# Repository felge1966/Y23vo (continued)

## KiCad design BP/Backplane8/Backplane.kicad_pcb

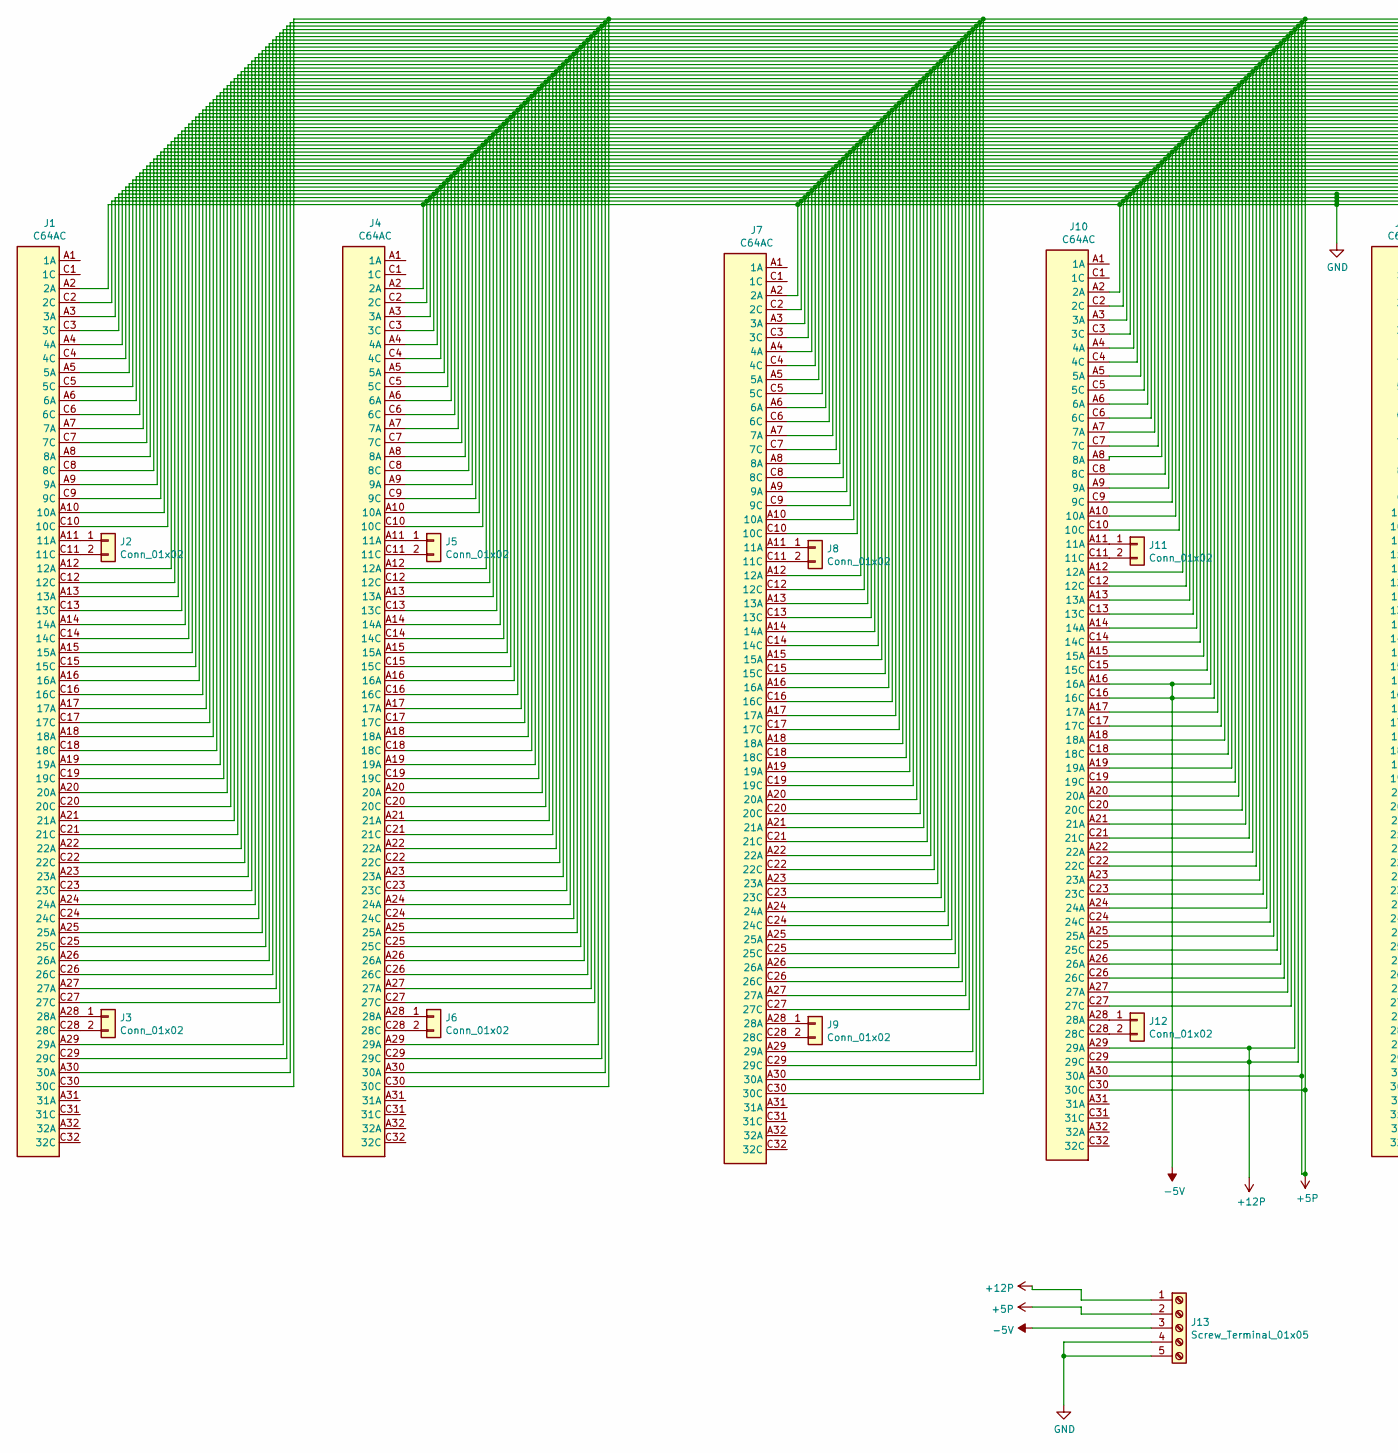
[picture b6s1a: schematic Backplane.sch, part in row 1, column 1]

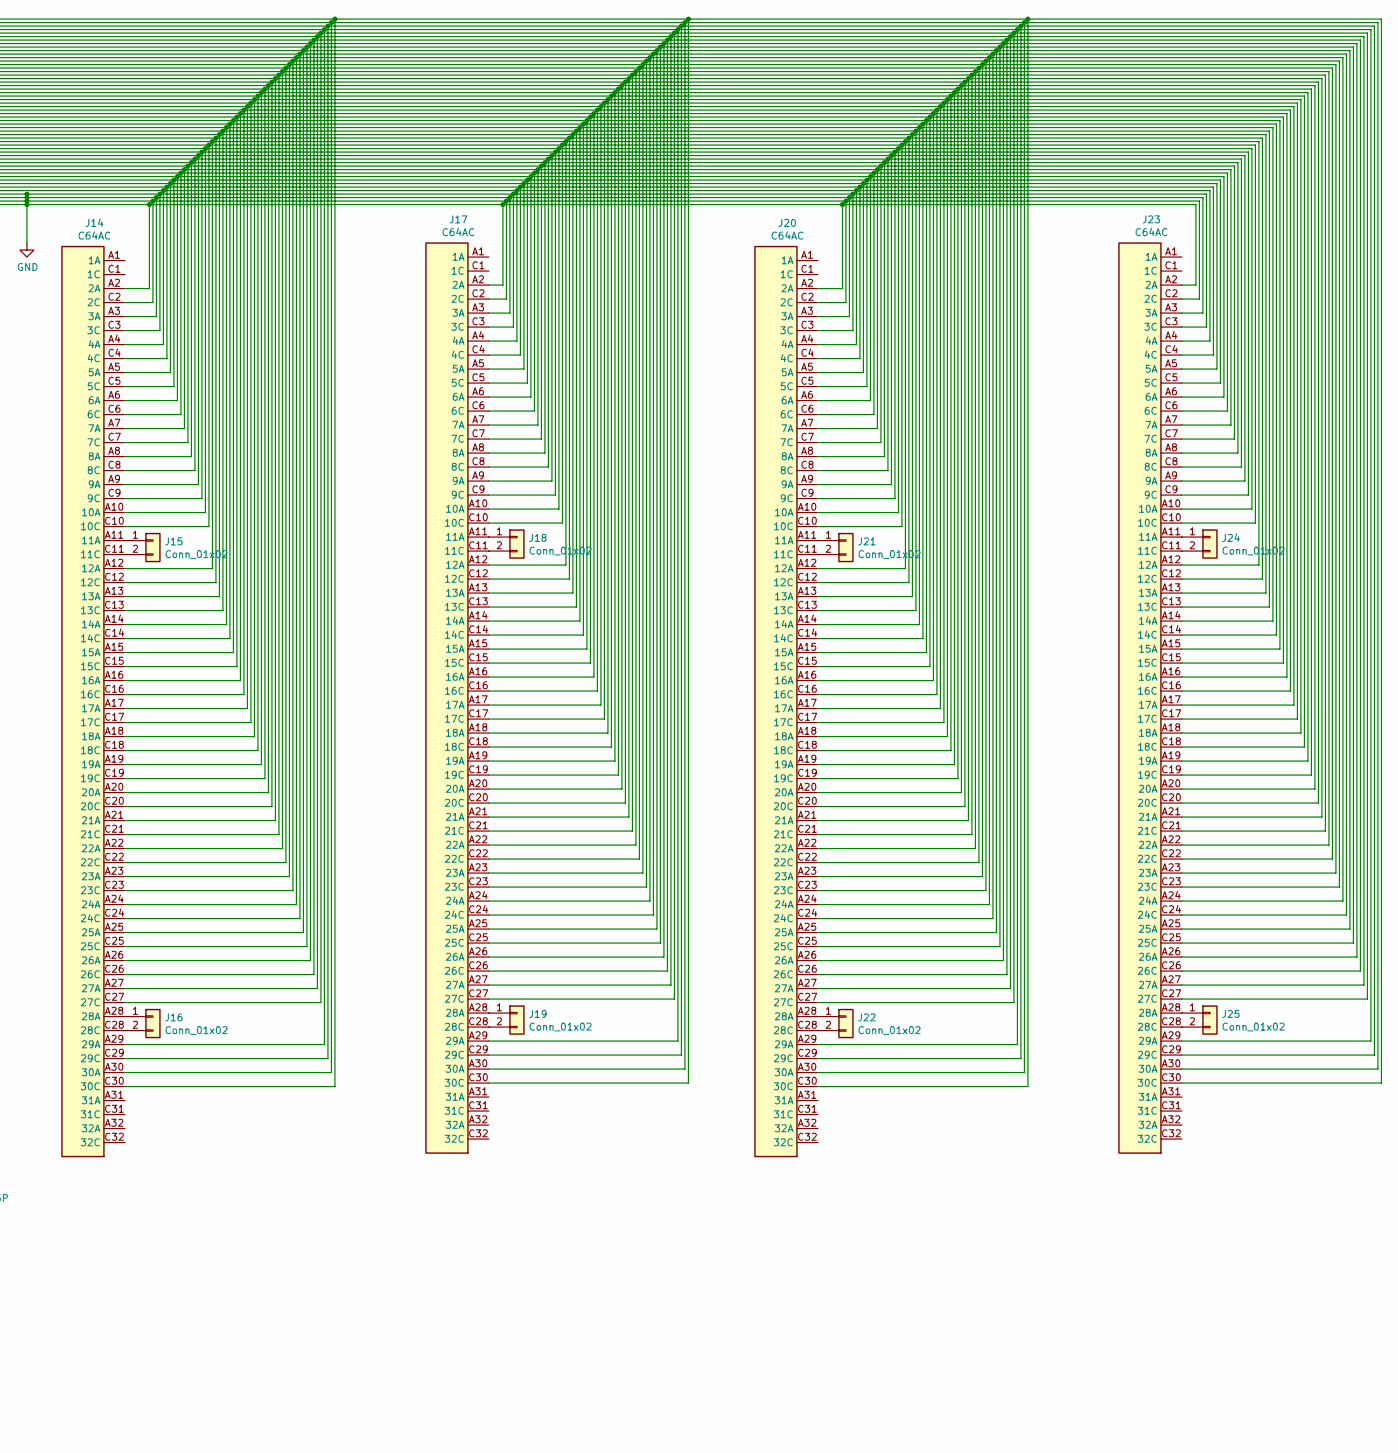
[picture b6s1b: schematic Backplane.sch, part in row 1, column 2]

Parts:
J1, J4, J7, J10, J14, J17, J20, J23: C64AC; DIN41612_C_3x32_Female_Vertical_THT-Gross
J2, J3, J5, J6, J8, J9, J11, J12, J15, J16, J18, J19, J21, J22, J24, J25: Conn_01x02; PinSocket_1x02_P2.54mm_Vertical
J13: Screw_Terminal_01x05; JST_EH_B5B-EH-A_1x05_P2.50mm_Vertical

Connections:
+5P: J1.A30 (30A), J1.C30 (30C), J4.A30 (30A), J4.C30 (30C), J7.A30 (30A), J7.C30 (30C), J10.A30 (30A), J10.C30 (30C), J13.2, J14.A30 (30A), J14.C30 (30C), J17.A30 (30A), J17.C30 (30C), J20.A30 (30A), J20.C30 (30C), J23.A30 (30A), J23.C30 (30C)
+12P: J1.A29 (29A), J1.C29 (29C), J4.A29 (29A), J4.C29 (29C), J7.A29 (29A), J7.C29 (29C), J10.A29 (29A), J10.C29 (29C), J13.1, J14.A29 (29A), J14.C29 (29C), J17.A29 (29A), J17.C29 (29C), J20.A29 (29A), J20.C29 (29C), J23.A29 (29A), J23.C29 (29C)
-5V: J1.A16 (16A), J1.C16 (16C), J4.A16 (16A), J4.C16 (16C), J7.A16 (16A), J7.C16 (16C), J10.A16 (16A), J10.C16 (16C), J13.3, J14.A16 (16A), J14.C16 (16C), J17.A16 (16A), J17.C16 (16C), J20.A16 (16A), J20.C16 (16C), J23.A16 (16A), J23.C16 (16C)
GND: J1.A2 (2A), J1.A3 (3A), J1.C2 (2C), J1.C3 (3C), J4.A2 (2A), J4.A3 (3A), J4.C2 (2C), J4.C3 (3C), J7.A2 (2A), J7.A3 (3A), J7.C2 (2C), J7.C3 (3C), J10.A2 (2A), J10.A3 (3A), J10.C2 (2C), J10.C3 (3C), J13.4, J13.5, J14.A2 (2A), J14.A3 (3A), J14.C2 (2C), J14.C3 (3C), J17.A2 (2A), J17.A3 (3A), J17.C2 (2C), J17.C3 (3C), J20.A2 (2A), J20.A3 (3A), J20.C2 (2C), J20.C3 (3C), J23.A2 (2A), J23.A3 (3A), J23.C2 (2C), J23.C3 (3C)
unnamed: J1.A4 (4A), J4.A4 (4A), J7.A4 (4A), J10.A4 (4A), J14.A4 (4A), J17.A4 (4A), J20.A4 (4A), J23.A4 (4A)
unnamed: J1.A5 (5A), J4.A5 (5A), J7.A5 (5A), J10.A5 (5A), J14.A5 (5A), J17.A5 (5A), J20.A5 (5A), J23.A5 (5A)
unnamed: J1.A6 (6A), J4.A6 (6A), J7.A6 (6A), J10.A6 (6A), J14.A6 (6A), J17.A6 (6A), J20.A6 (6A), J23.A6 (6A)
unnamed: J1.A7 (7A), J4.A7 (7A), J7.A7 (7A), J10.A7 (7A), J14.A7 (7A), J17.A7 (7A), J20.A7 (7A), J23.A7 (7A)
unnamed: J1.A8 (8A), J4.A8 (8A), J7.A8 (8A), J10.A8 (8A), J14.A8 (8A), J17.A8 (8A), J20.A8 (8A), J23.A8 (8A)
unnamed: J1.A9 (9A), J4.A9 (9A), J7.A9 (9A), J10.A9 (9A), J14.A9 (9A), J17.A9 (9A), J20.A9 (9A), J23.A9 (9A)
unnamed: J1.A10 (10A), J4.A10 (10A), J7.A10 (10A), J10.A10 (10A), J14.A10 (10A), J17.A10 (10A), J20.A10 (10A), J23.A10 (10A)
unnamed: J1.A11 (11A), J2.1
unnamed: J1.A12 (12A), J4.A12 (12A), J7.A12 (12A), J10.A12 (12A), J14.A12 (12A), J17.A12 (12A), J20.A12 (12A), J23.A12 (12A)
unnamed: J1.A13 (13A), J4.A13 (13A), J7.A13 (13A), J10.A13 (13A), J14.A13 (13A), J17.A13 (13A), J20.A13 (13A), J23.A13 (13A)
unnamed: J1.A14 (14A), J4.A14 (14A), J7.A14 (14A), J10.A14 (14A), J14.A14 (14A), J17.A14 (14A), J20.A14 (14A), J23.A14 (14A)
unnamed: J1.A15 (15A), J4.A15 (15A), J7.A15 (15A), J10.A15 (15A), J14.A15 (15A), J17.A15 (15A), J20.A15 (15A), J23.A15 (15A)
unnamed: J1.A17 (17A), J4.A17 (17A), J7.A17 (17A), J10.A17 (17A), J14.A17 (17A), J17.A17 (17A), J20.A17 (17A), J23.A17 (17A)
unnamed: J1.A18 (18A), J4.A18 (18A), J7.A18 (18A), J10.A18 (18A), J14.A18 (18A), J17.A18 (18A), J20.A18 (18A), J23.A18 (18A)
unnamed: J1.A19 (19A), J4.A19 (19A), J7.A19 (19A), J10.A19 (19A), J14.A19 (19A), J17.A19 (19A), J20.A19 (19A), J23.A19 (19A)
unnamed: J1.A20 (20A), J4.A20 (20A), J7.A20 (20A), J10.A20 (20A), J14.A20 (20A), J17.A20 (20A), J20.A20 (20A), J23.A20 (20A)
unnamed: J1.A21 (21A), J4.A21 (21A), J7.A21 (21A), J10.A21 (21A), J14.A21 (21A), J17.A21 (21A), J20.A21 (21A), J23.A21 (21A)
unnamed: J1.A22 (22A), J4.A22 (22A), J7.A22 (22A), J10.A22 (22A), J14.A22 (22A), J17.A22 (22A), J20.A22 (22A), J23.A22 (22A)
unnamed: J1.A23 (23A), J4.A23 (23A), J7.A23 (23A), J10.A23 (23A), J14.A23 (23A), J17.A23 (23A), J20.A23 (23A), J23.A23 (23A)
unnamed: J1.A24 (24A), J4.A24 (24A), J7.A24 (24A), J10.A24 (24A), J14.A24 (24A), J17.A24 (24A), J20.A24 (24A), J23.A24 (24A)
unnamed: J1.A25 (25A), J4.A25 (25A), J7.A25 (25A), J10.A25 (25A), J14.A25 (25A), J17.A25 (25A), J20.A25 (25A), J23.A25 (25A)
unnamed: J1.A26 (26A), J4.A26 (26A), J7.A26 (26A), J10.A26 (26A), J14.A26 (26A), J17.A26 (26A), J20.A26 (26A), J23.A26 (26A)
unnamed: J1.A27 (27A), J4.A27 (27A), J7.A27 (27A), J10.A27 (27A), J14.A27 (27A), J17.A27 (27A), J20.A27 (27A), J23.A27 (27A)
unnamed: J1.A28 (28A), J3.1
unnamed: J1.C4 (4C), J4.C4 (4C), J7.C4 (4C), J10.C4 (4C), J14.C4 (4C), J17.C4 (4C), J20.C4 (4C), J23.C4 (4C)
unnamed: J1.C5 (5C), J4.C5 (5C), J7.C5 (5C), J10.C5 (5C), J14.C5 (5C), J17.C5 (5C), J20.C5 (5C), J23.C5 (5C)
unnamed: J1.C6 (6C), J4.C6 (6C), J7.C6 (6C), J10.C6 (6C), J14.C6 (6C), J17.C6 (6C), J20.C6 (6C), J23.C6 (6C)
unnamed: J1.C7 (7C), J4.C7 (7C), J7.C7 (7C), J10.C7 (7C), J14.C7 (7C), J17.C7 (7C), J20.C7 (7C), J23.C7 (7C)
unnamed: J1.C8 (8C), J4.C8 (8C), J7.C8 (8C), J10.C8 (8C), J14.C8 (8C), J17.C8 (8C), J20.C8 (8C), J23.C8 (8C)
unnamed: J1.C9 (9C), J4.C9 (9C), J7.C9 (9C), J10.C9 (9C), J14.C9 (9C), J17.C9 (9C), J20.C9 (9C), J23.C9 (9C)
unnamed: J1.C10 (10C), J4.C10 (10C), J7.C10 (10C), J10.C10 (10C), J14.C10 (10C), J17.C10 (10C), J20.C10 (10C), J23.C10 (10C)
unnamed: J1.C11 (11C), J2.2
unnamed: J1.C12 (12C), J4.C12 (12C), J7.C12 (12C), J10.C12 (12C), J14.C12 (12C), J17.C12 (12C), J20.C12 (12C), J23.C12 (12C)
unnamed: J1.C13 (13C), J4.C13 (13C), J7.C13 (13C), J10.C13 (13C), J14.C13 (13C), J17.C13 (13C), J20.C13 (13C), J23.C13 (13C)
unnamed: J1.C14 (14C), J4.C14 (14C), J7.C14 (14C), J10.C14 (14C), J14.C14 (14C), J17.C14 (14C), J20.C14 (14C), J23.C14 (14C)
unnamed: J1.C15 (15C), J4.C15 (15C), J7.C15 (15C), J10.C15 (15C), J14.C15 (15C), J17.C15 (15C), J20.C15 (15C), J23.C15 (15C)
unnamed: J1.C17 (17C), J4.C17 (17C), J7.C17 (17C), J10.C17 (17C), J14.C17 (17C), J17.C17 (17C), J20.C17 (17C), J23.C17 (17C)
unnamed: J1.C18 (18C), J4.C18 (18C), J7.C18 (18C), J10.C18 (18C), J14.C18 (18C), J17.C18 (18C), J20.C18 (18C), J23.C18 (18C)
unnamed: J1.C19 (19C), J4.C19 (19C), J7.C19 (19C), J10.C19 (19C), J14.C19 (19C), J17.C19 (19C), J20.C19 (19C), J23.C19 (19C)
unnamed: J1.C20 (20C), J4.C20 (20C), J7.C20 (20C), J10.C20 (20C), J14.C20 (20C), J17.C20 (20C), J20.C20 (20C), J23.C20 (20C)
unnamed: J1.C21 (21C), J4.C21 (21C), J7.C21 (21C), J10.C21 (21C), J14.C21 (21C), J17.C21 (21C), J20.C21 (21C), J23.C21 (21C)
unnamed: J1.C22 (22C), J4.C22 (22C), J7.C22 (22C), J10.C22 (22C), J14.C22 (22C), J17.C22 (22C), J20.C22 (22C), J23.C22 (22C)
unnamed: J1.C23 (23C), J4.C23 (23C), J7.C23 (23C), J10.C23 (23C), J14.C23 (23C), J17.C23 (23C), J20.C23 (23C), J23.C23 (23C)
unnamed: J1.C24 (24C), J4.C24 (24C), J7.C24 (24C), J10.C24 (24C), J14.C24 (24C), J17.C24 (24C), J20.C24 (24C), J23.C24 (24C)
unnamed: J1.C25 (25C), J4.C25 (25C), J7.C25 (25C), J10.C25 (25C), J14.C25 (25C), J17.C25 (25C), J20.C25 (25C), J23.C25 (25C)
unnamed: J1.C26 (26C), J4.C26 (26C), J7.C26 (26C), J10.C26 (26C), J14.C26 (26C), J17.C26 (26C), J20.C26 (26C), J23.C26 (26C)
unnamed: J1.C27 (27C), J4.C27 (27C), J7.C27 (27C), J10.C27 (27C), J14.C27 (27C), J17.C27 (27C), J20.C27 (27C), J23.C27 (27C)
unnamed: J1.C28 (28C), J3.2
unnamed: J4.A11 (11A), J5.1
unnamed: J4.A28 (28A), J6.1
unnamed: J4.C11 (11C), J5.2
unnamed: J4.C28 (28C), J6.2
unnamed: J7.A11 (11A), J8.1
unnamed: J7.A28 (28A), J9.1
unnamed: J7.C11 (11C), J8.2
unnamed: J7.C28 (28C), J9.2
unnamed: J10.A11 (11A), J11.1
unnamed: J10.A28 (28A), J12.1
unnamed: J10.C11 (11C), J11.2
unnamed: J10.C28 (28C), J12.2
unnamed: J14.A11 (11A), J15.1
unnamed: J14.A28 (28A), J16.1
unnamed: J14.C11 (11C), J15.2
unnamed: J14.C28 (28C), J16.2
unnamed: J17.A11 (11A), J18.1
unnamed: J17.A28 (28A), J19.1
unnamed: J17.C11 (11C), J18.2
unnamed: J17.C28 (28C), J19.2
unnamed: J20.A11 (11A), J21.1
unnamed: J20.A28 (28A), J22.1
unnamed: J20.C11 (11C), J21.2
unnamed: J20.C28 (28C), J22.2
unnamed: J23.A11 (11A), J24.1
unnamed: J23.A28 (28A), J25.1
unnamed: J23.C11 (11C), J24.2
unnamed: J23.C28 (28C), J25.2

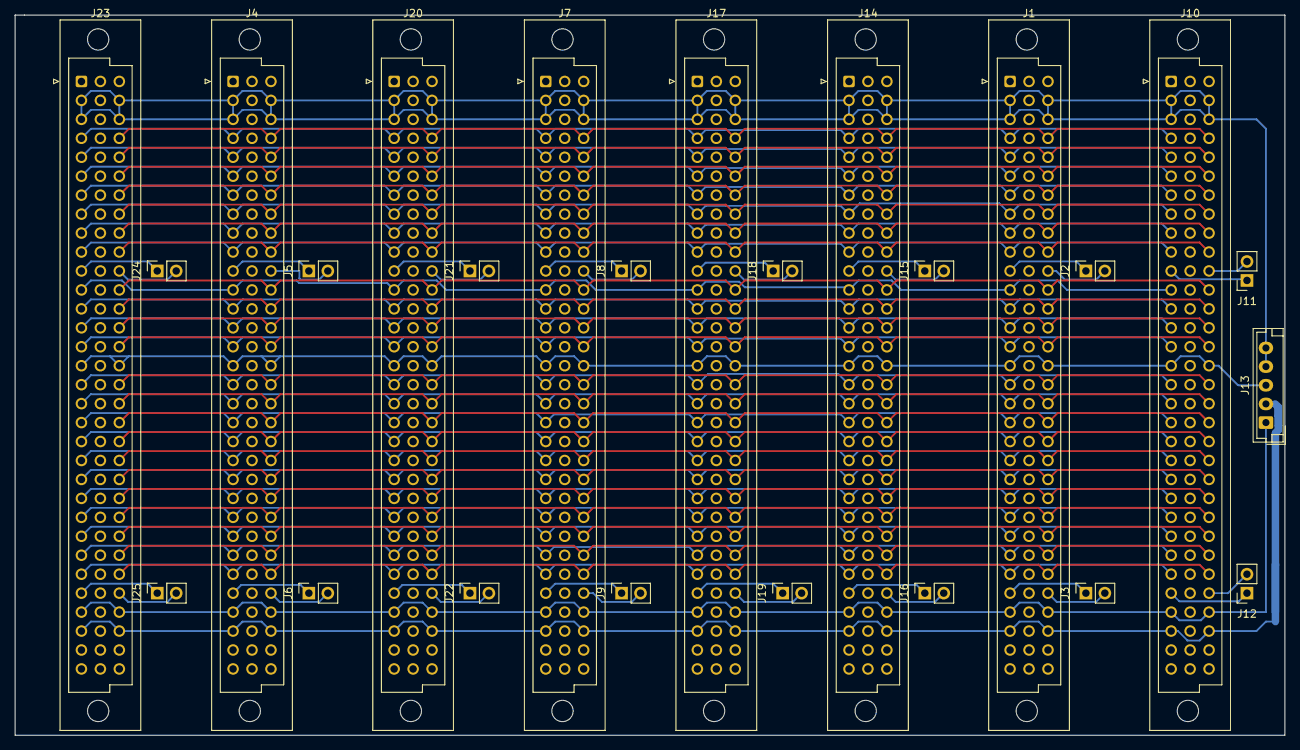
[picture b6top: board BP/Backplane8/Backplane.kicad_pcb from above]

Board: 2 copper layers, 170.2 x 96.5 mm, 25 parts (0 on the bottom side), 80 nets.
